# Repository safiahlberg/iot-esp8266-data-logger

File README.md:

# iot-esp8266-data-logger
IoT Data Logger for ESP8266

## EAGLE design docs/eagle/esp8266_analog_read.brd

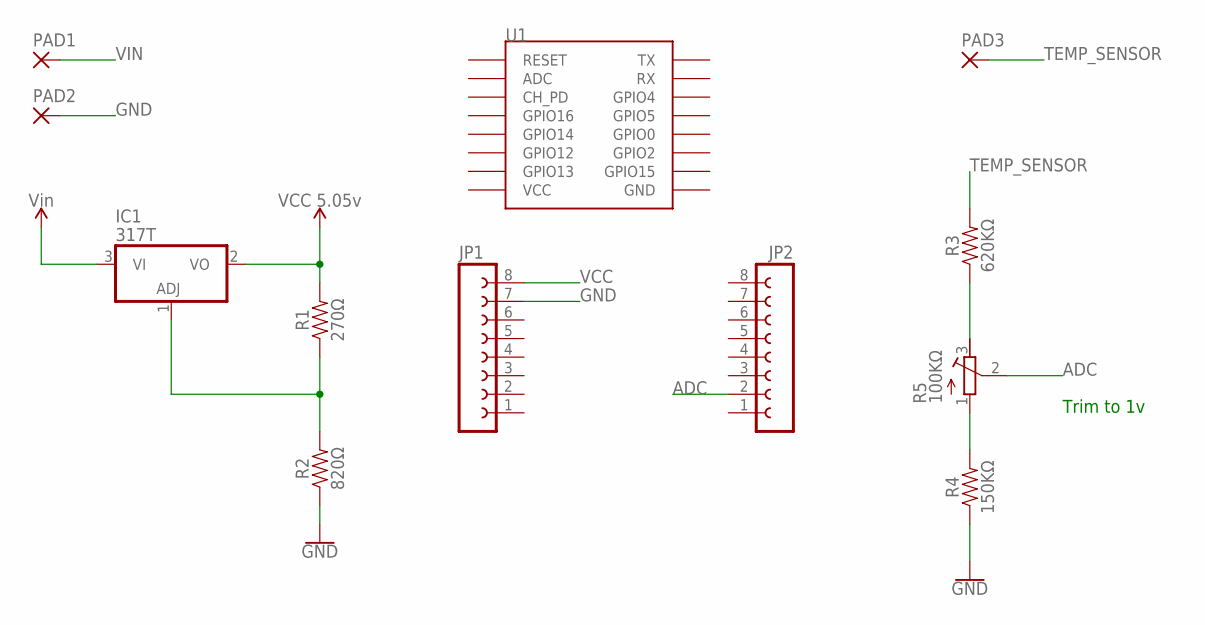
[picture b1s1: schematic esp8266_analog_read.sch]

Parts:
IC1: 317T; TO220H
JP1, JP2: FE08-1; FE08
PAD1, PAD2, PAD3: 2,54/1,0
R1: 270Ω; AXIAL-0.3
R2: 820Ω; AXIAL-0.3
R3: 620KΩ; AXIAL-0.3
R4: 150KΩ; AXIAL-0.3
R5: 100KΩ; RTRIM3339P
U1: ESP12

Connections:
ADC: JP2.2, R5.2 (S)
GND: JP1.7, PAD2.1, R2.P$1 (1), R4.P$1 (1)
unnamed: R3.P$1 (1), R5.3 (E)
unnamed: R4.P$2 (2), R5.1 (A)
unnamed: IC1.1 (ADJ), R1.P$1 (1), R2.P$2 (2)
TEMP_SENSOR: PAD3.1, R3.P$2 (2)
VCC: IC1.2 (VO), JP1.8, R1.P$2 (2)
VIN: IC1.3 (VI), PAD1.1

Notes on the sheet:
Trim to 1v

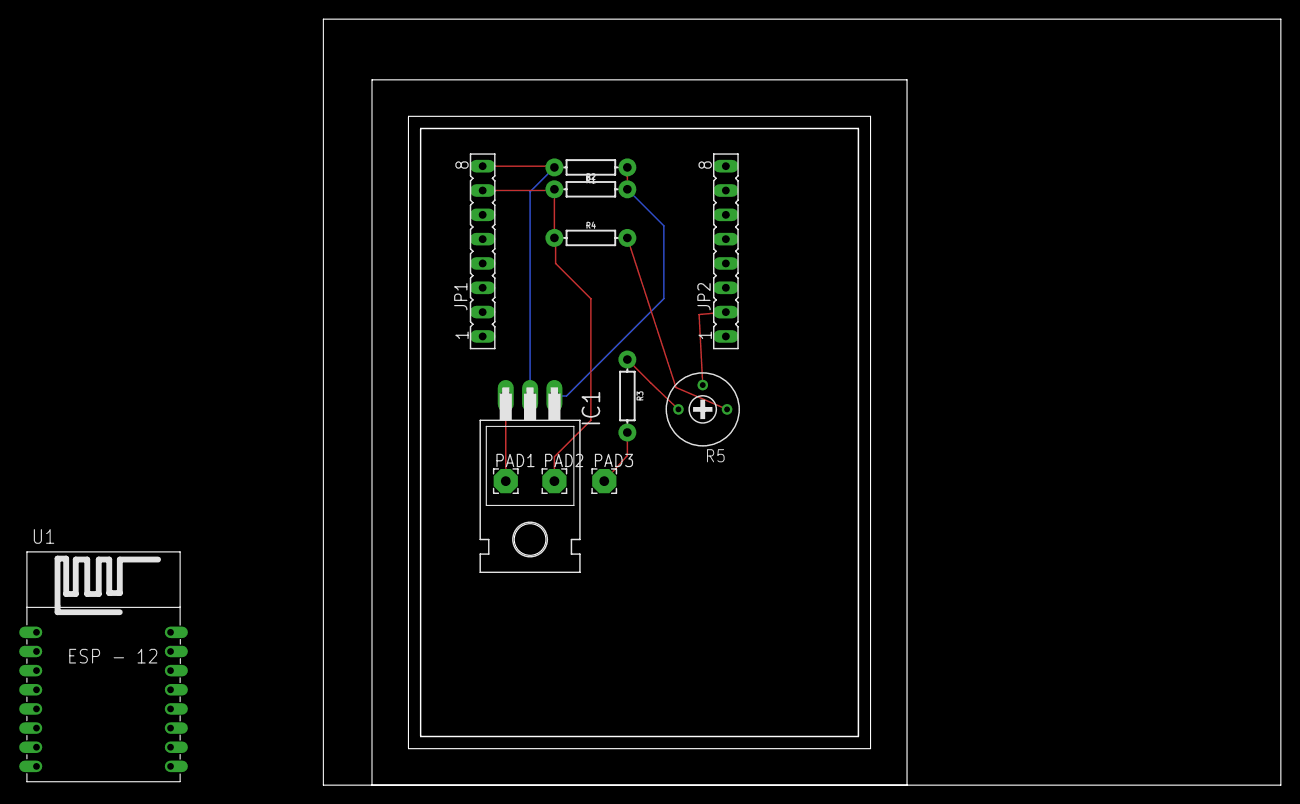
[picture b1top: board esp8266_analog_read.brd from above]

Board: 2 copper layers, 100.0 x 80.0 mm, 12 parts (0 on the bottom side), 8 nets.

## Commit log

2017-09-02 Added to gitignore
2017-09-02 Initial rev
2017-09-02 Added information on what needs to be defined in private_data.h
2017-09-02 Moved sketch to separate directory
2017-09-02 Removed outdated key
2017-09-02 Added flowchart
2017-09-02 Added loop flow
2017-09-02 Moved flowchart to separate directory
2017-09-02 Added ignore for eagle temp files
2017-09-02 Added Eagle files for schematics and prototype board
2017-09-02 Added explanation for some gitignore rows
2017-09-03 Added colors
2017-09-12 New directory structure for Yakindu (Eclipse)
2017-09-12 Added some files from Arduino example in Yakindu
2017-09-14 Added iot_datalogger.xml
2017-09-14 Added void declaration to avoid compile errors from Eclipse (Yakindu)
2017-09-14 Added a statechart and generation schema.
2017-09-14 Revert "Added iot_datalogger.xml"
    This reverts commit 00562b7db0a4ae77fa81694ea9ee77dfab482ce3.
2017-09-15 Added events.
2017-09-15 Deleted directory src-gen and added it to gitignore
2017-09-16 Added some more refinements around initialisation
2017-09-16 Simplified some display events
2017-09-17 Minor adjustments
2017-09-21 Added some operations for the long running activities of WiFi connection, MQTT Connection and MQTT fingerprint verification.
2017-09-25 Refining activities
2017-09-27 Added code to arduino sketch
2017-09-27 Removed a faulty reference
2017-09-27 Fixed stubs for callbacks

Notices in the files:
parts and their libraries:
SparkFun-Resistors: Licensing: Creative Commons ShareAlike 4.0 International - https://creativecommons.org/licenses/by-sa/4.0
